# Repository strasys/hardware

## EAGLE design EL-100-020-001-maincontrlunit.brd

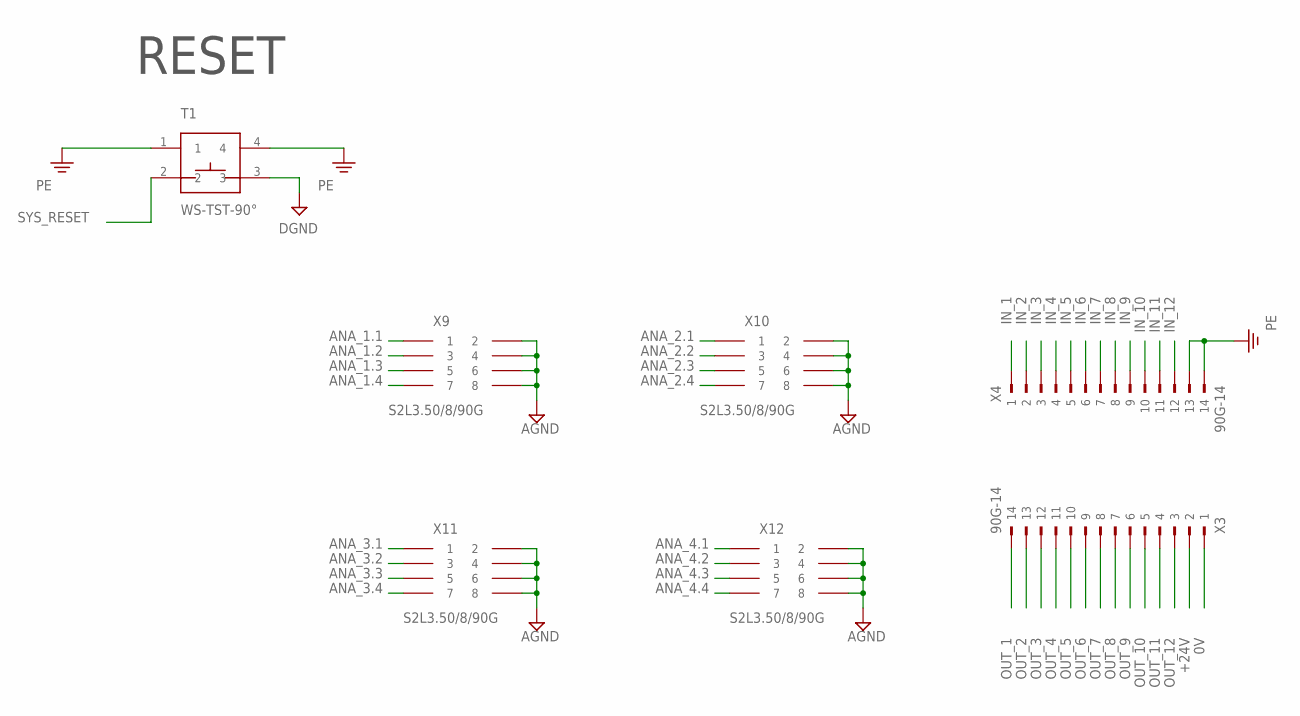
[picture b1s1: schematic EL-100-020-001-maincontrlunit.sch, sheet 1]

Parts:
T1: WS-TST-90°
X3, X4: 90G-14
X9, X10, X11, X12: S2L3.50/8/90G; S2L-90G-8

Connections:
0V: X3.1; also elsewhere on the board
+24V: X3.2; also elsewhere on the board
AGND: X9.2, X9.4, X9.6, X9.8, X10.2, X10.4, X10.6, X10.8, X11.2, X11.4, X11.6, X11.8, X12.2, X12.4, X12.6, X12.8; also elsewhere on the board
ANA_1.1: X9.1; also elsewhere on the board
ANA_1.2: X9.3; also elsewhere on the board
ANA_1.3: X9.5; also elsewhere on the board
ANA_1.4: X9.7; also elsewhere on the board
ANA_2.1: X10.1; also elsewhere on the board
ANA_2.2: X10.3; also elsewhere on the board
ANA_2.3: X10.5; also elsewhere on the board
ANA_2.4: X10.7; also elsewhere on the board
ANA_3.1: X11.1; also elsewhere on the board
ANA_3.2: X11.3; also elsewhere on the board
ANA_3.3: X11.5; also elsewhere on the board
ANA_3.4: X11.7; also elsewhere on the board
ANA_4.1: X12.1; also elsewhere on the board
ANA_4.2: X12.3; also elsewhere on the board
ANA_4.3: X12.5; also elsewhere on the board
ANA_4.4: X12.7; also elsewhere on the board
DGND: T1.3; also elsewhere on the board
IN_1: X4.1; also elsewhere on the board
IN_2: X4.2; also elsewhere on the board
IN_3: X4.3; also elsewhere on the board
IN_4: X4.4; also elsewhere on the board
IN_5: X4.5; also elsewhere on the board
IN_6: X4.6; also elsewhere on the board
IN_7: X4.7; also elsewhere on the board
IN_8: X4.8; also elsewhere on the board
IN_9: X4.9; also elsewhere on the board
IN_10: X4.10; also elsewhere on the board
IN_11: X4.11; also elsewhere on the board
IN_12: X4.12; also elsewhere on the board
OUT_1: X3.14; also elsewhere on the board
OUT_2: X3.13; also elsewhere on the board
OUT_3: X3.12; also elsewhere on the board
OUT_4: X3.11; also elsewhere on the board
OUT_5: X3.10; also elsewhere on the board
OUT_6: X3.9; also elsewhere on the board
OUT_7: X3.8; also elsewhere on the board
OUT_8: X3.7; also elsewhere on the board
OUT_9: X3.6; also elsewhere on the board
OUT_10: X3.5; also elsewhere on the board
OUT_11: X3.4; also elsewhere on the board
OUT_12: X3.3; also elsewhere on the board
PE: T1.1, T1.4, X4.13, X4.14; also elsewhere on the board
SYS_RESET: T1.2; also elsewhere on the board

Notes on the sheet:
RESET

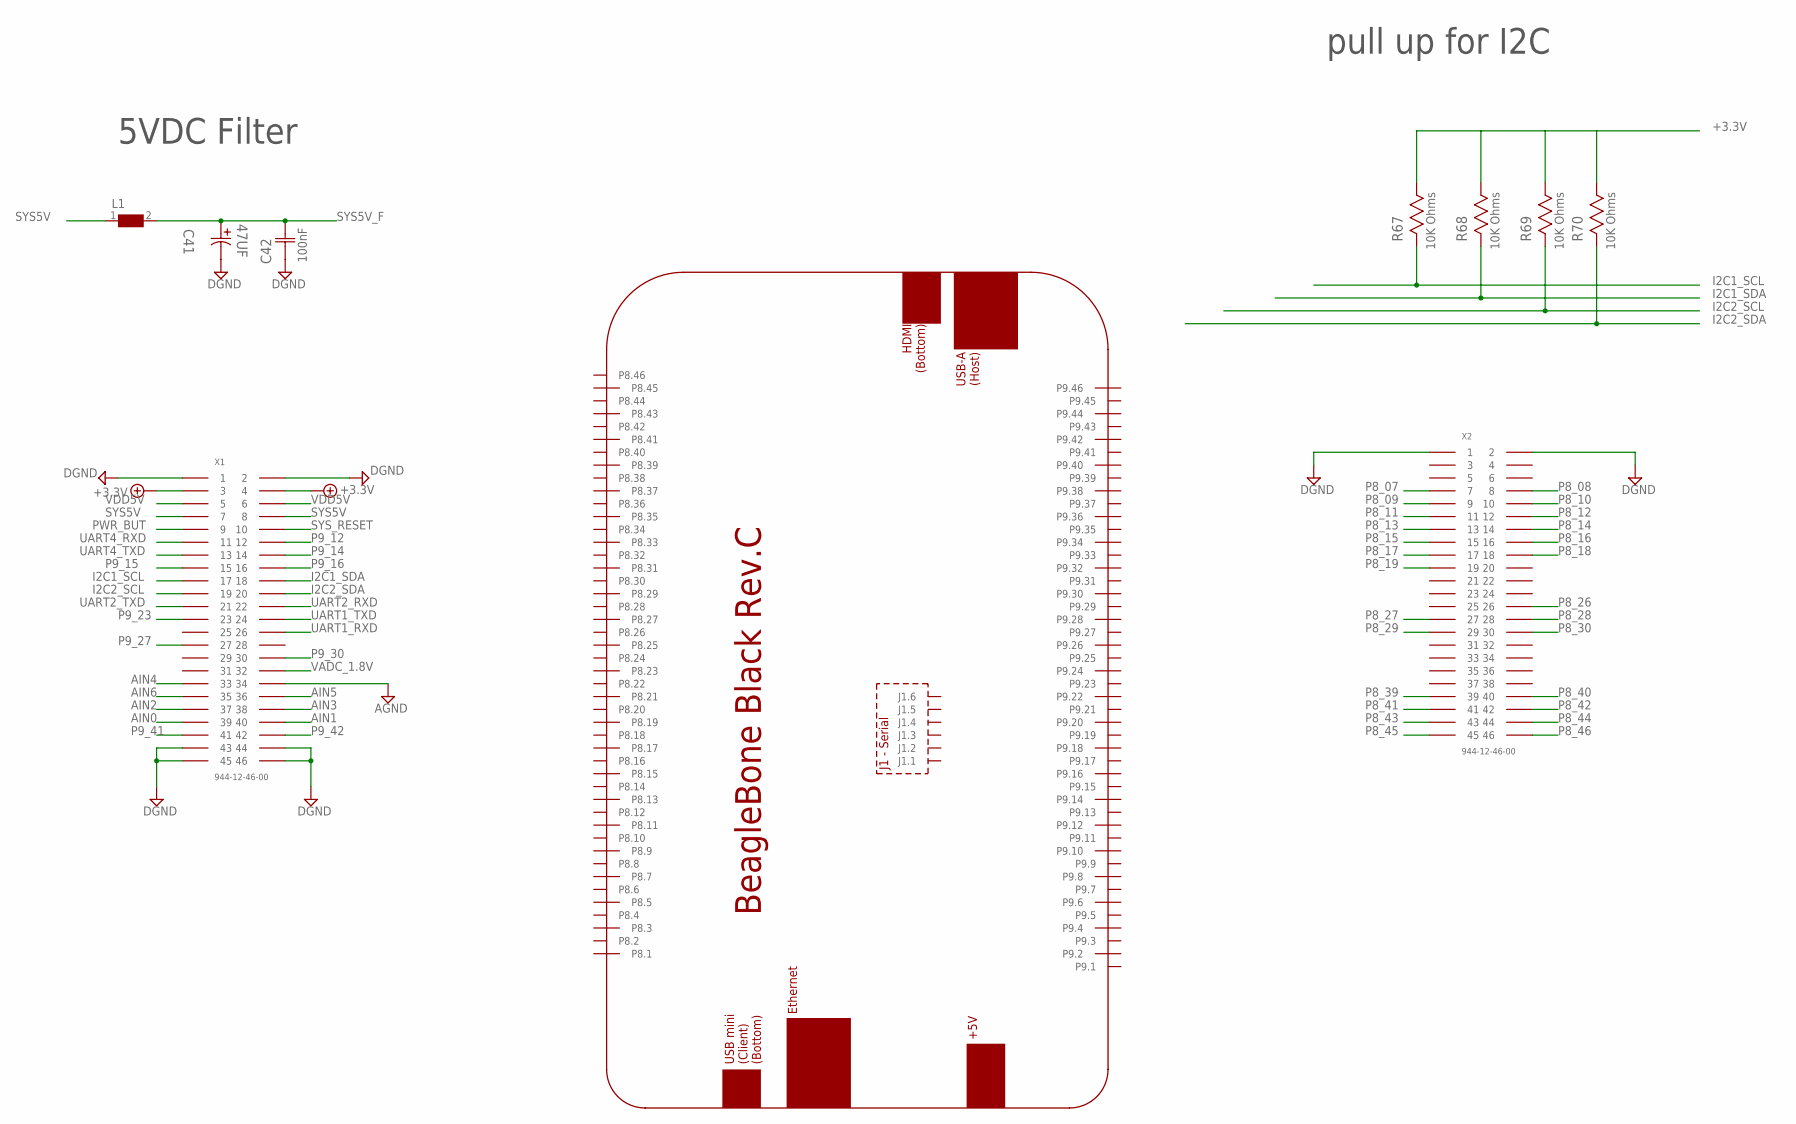
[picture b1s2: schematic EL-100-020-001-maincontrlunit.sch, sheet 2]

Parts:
C41: 47UF; CAPAE660X610N
C42: 100nF; CAPC2013X110N
L1: WE-CBF-74279218_1206; 1206
R67, R68, R69, R70: 10K Ohms; RESC2013X65N
X1, X2: 944-12-46-00; 2,54_STIFTLEIST_2X23

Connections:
+3.3V: R67.1, R68.1, R69.1, R70.1, X1.P3 (3), X1.P4 (4); also elsewhere on the board
AGND: X1.P34 (34); also elsewhere on the board
AIN0: X1.P39 (39); also elsewhere on the board
AIN1: X1.P40 (40); also elsewhere on the board
AIN2: X1.P37 (37); also elsewhere on the board
AIN3: X1.P38 (38); also elsewhere on the board
AIN4: X1.P33 (33); also elsewhere on the board
AIN5: X1.P36 (36); also elsewhere on the board
AIN6: X1.P35 (35); also elsewhere on the board
DGND: C41.2, C42.1 (C1), X1.P1 (1), X1.P2 (2), X1.P43 (43), X1.P44 (44), X1.P45 (45), X1.P46 (46), X2.P1 (1), X2.P2 (2); also elsewhere on the board
I2C1_SCL: R67.2, X1.P17 (17); also elsewhere on the board
I2C1_SDA: R68.2, X1.P18 (18); also elsewhere on the board
I2C2_SCL: R69.2, X1.P19 (19); also elsewhere on the board
I2C2_SDA: R70.2, X1.P20 (20); also elsewhere on the board
P8_07: X2.P7 (7); also elsewhere on the board
P8_08: X2.P8 (8); also elsewhere on the board
P8_09: X2.P9 (9); also elsewhere on the board
P8_10: X2.P10 (10); also elsewhere on the board
P8_11: X2.P11 (11); also elsewhere on the board
P8_12: X2.P12 (12); also elsewhere on the board
P8_13: X2.P13 (13); also elsewhere on the board
P8_14: X2.P14 (14); also elsewhere on the board
P8_15: X2.P15 (15); also elsewhere on the board
P8_16: X2.P16 (16); also elsewhere on the board
P8_17: X2.P17 (17); also elsewhere on the board
P8_18: X2.P18 (18); also elsewhere on the board
P8_19: X2.P19 (19)
P8_26: X2.P26 (26)
P8_27: X2.P27 (27); also elsewhere on the board
P8_28: X2.P28 (28); also elsewhere on the board
P8_29: X2.P29 (29); also elsewhere on the board
P8_30: X2.P30 (30); also elsewhere on the board
P8_39: X2.P39 (39); also elsewhere on the board
P8_40: X2.P40 (40); also elsewhere on the board
P8_41: X2.P41 (41); also elsewhere on the board
P8_42: X2.P42 (42); also elsewhere on the board
P8_43: X2.P43 (43); also elsewhere on the board
P8_44: X2.P44 (44); also elsewhere on the board
P8_45: X2.P45 (45); also elsewhere on the board
P8_46: X2.P46 (46); also elsewhere on the board
P9_12: X1.P12 (12)
P9_14: X1.P14 (14); also elsewhere on the board
P9_15: X1.P15 (15); also elsewhere on the board
P9_16: X1.P16 (16)
P9_23: X1.P23 (23)
P9_27: X1.P27 (27)
P9_30: X1.P30 (30)
P9_41: X1.P41 (41)
P9_42: X1.P42 (42)
PWR_BUT: X1.P9 (9)
SYS5V: L1.1, X1.P7 (7), X1.P8 (8)
SYS5V_F: C41.1, C42.2 (C2), L1.2; also elsewhere on the board
SYS_RESET: X1.P10 (10); also elsewhere on the board
UART1_RXD: X1.P26 (26)
UART1_TXD: X1.P24 (24)
UART2_RXD: X1.P22 (22)
UART2_TXD: X1.P21 (21)
UART4_RXD: X1.P11 (11)
UART4_TXD: X1.P13 (13)
VADC_1.8V: X1.P32 (32); also elsewhere on the board
VDD5V: X1.P5 (5), X1.P6 (6)

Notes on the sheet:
5VDC Filter
pull up for I2C

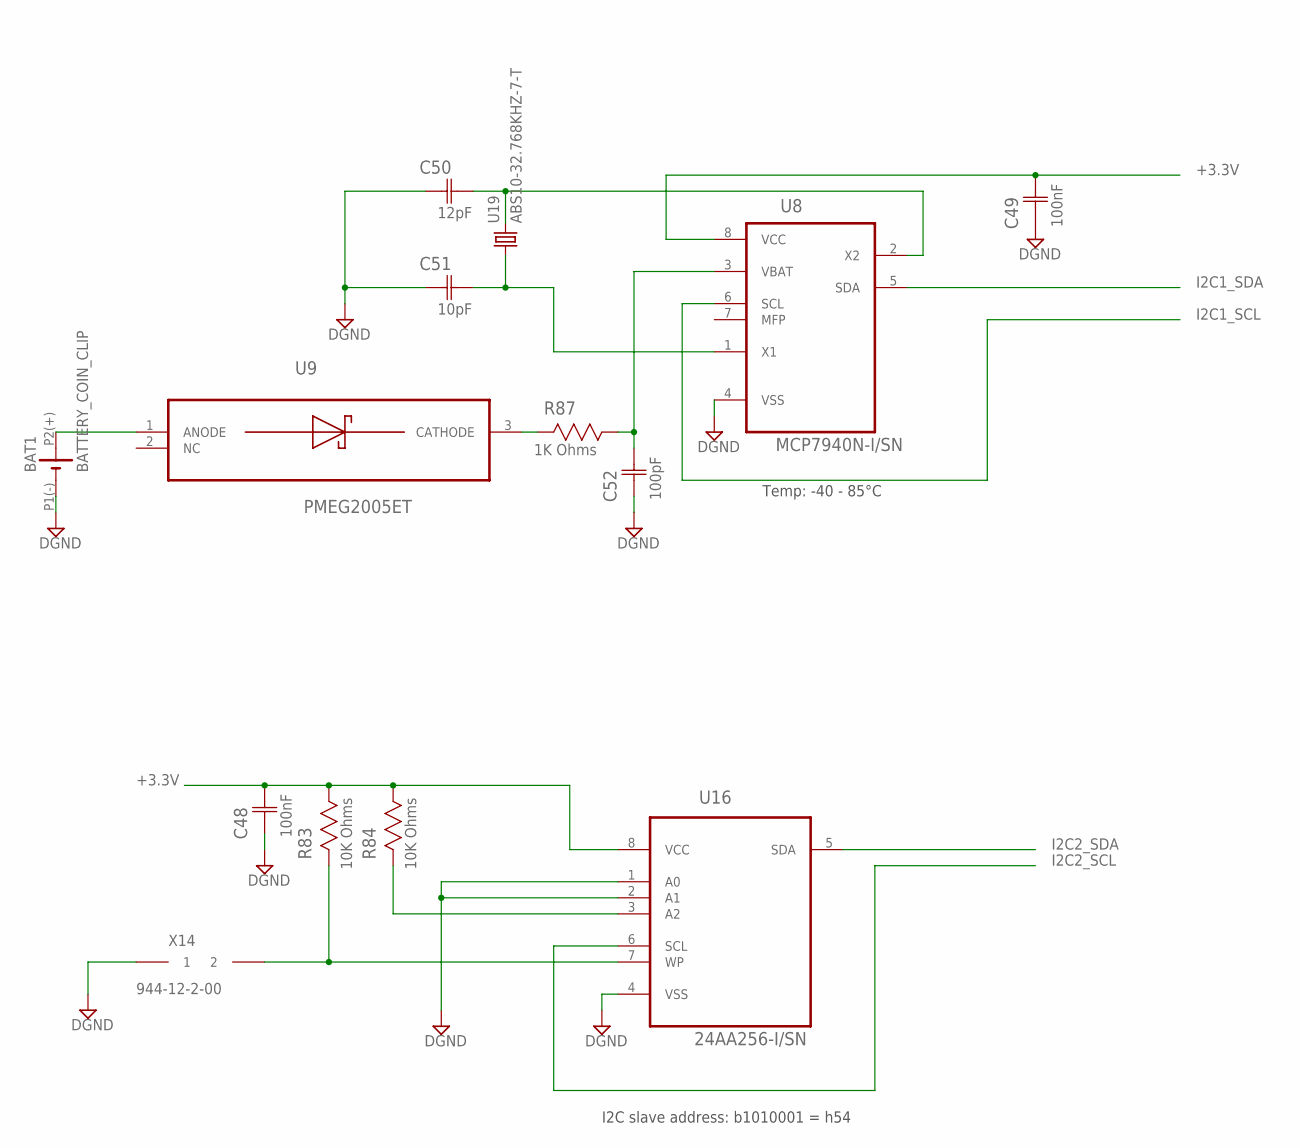
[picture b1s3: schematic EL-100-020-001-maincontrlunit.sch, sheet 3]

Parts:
BAT1: BATTERY_COIN_CLIP; BAT_HOLDER_16MM
C48, C49: 100nF; CAPC2013X110N
C50: 12pF; CAPC2013X88N
C51: 10pF; CAPC2013X88N
C52: 100pF; CAPC2013X88N
R83, R84: 10K Ohms; RESC2013X65N
R87: 1K Ohms; RESC2013X65N
U8: MCP7940N-I/SN; SOIC127P600X175-8N; MPN MCP7940N-I/SN
U9: PMEG2005ET; SOT95P280X145-5N
U16: 24AA256-I/SN; SOIC127P600X175-8N
U19: ABS10-32.768KHZ-7-T; ABS-10
X14: 944-12-2-00; 2,54_2X1

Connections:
24AA_WP: R83.2, U16.7 (WP), X14.P2 (2)
+3.3V: C48.2 (C2), C49.2 (C2), R83.1, R84.1, U8.8 (VCC), U16.8 (VCC); also elsewhere on the board
BAT-SUPPLY: BAT1.P2(+) (+), U9.1 (ANODE)
DGND: BAT1.P1(-) (-), C48.1 (C1), C49.1 (C1), C50.1 (C1), C51.1 (C1), C52.1 (C1), U8.4 (VSS), U16.1 (A0), U16.2 (A1), U16.4 (VSS), X14.P1 (1); also elsewhere on the board
I2C1_SCL: U8.6 (SCL); also elsewhere on the board
I2C1_SDA: U8.5 (SDA); also elsewhere on the board
I2C2_SCL: U16.6 (SCL); also elsewhere on the board
I2C2_SDA: U16.5 (SDA); also elsewhere on the board
unnamed: R84.2, U16.3 (A2)
unnamed: R87.2, U9.3 (CATHODE)
unnamed: C52.2 (C2), R87.1, U8.3 (VBAT)
unnamed: C50.2 (C2), U8.2 (X2), U19.P$2 (2)
unnamed: C51.2 (C2), U8.1 (X1), U19.P$1 (1)

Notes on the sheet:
Temp: -40 - 85°C
I2C slave address: b1010001 = h54

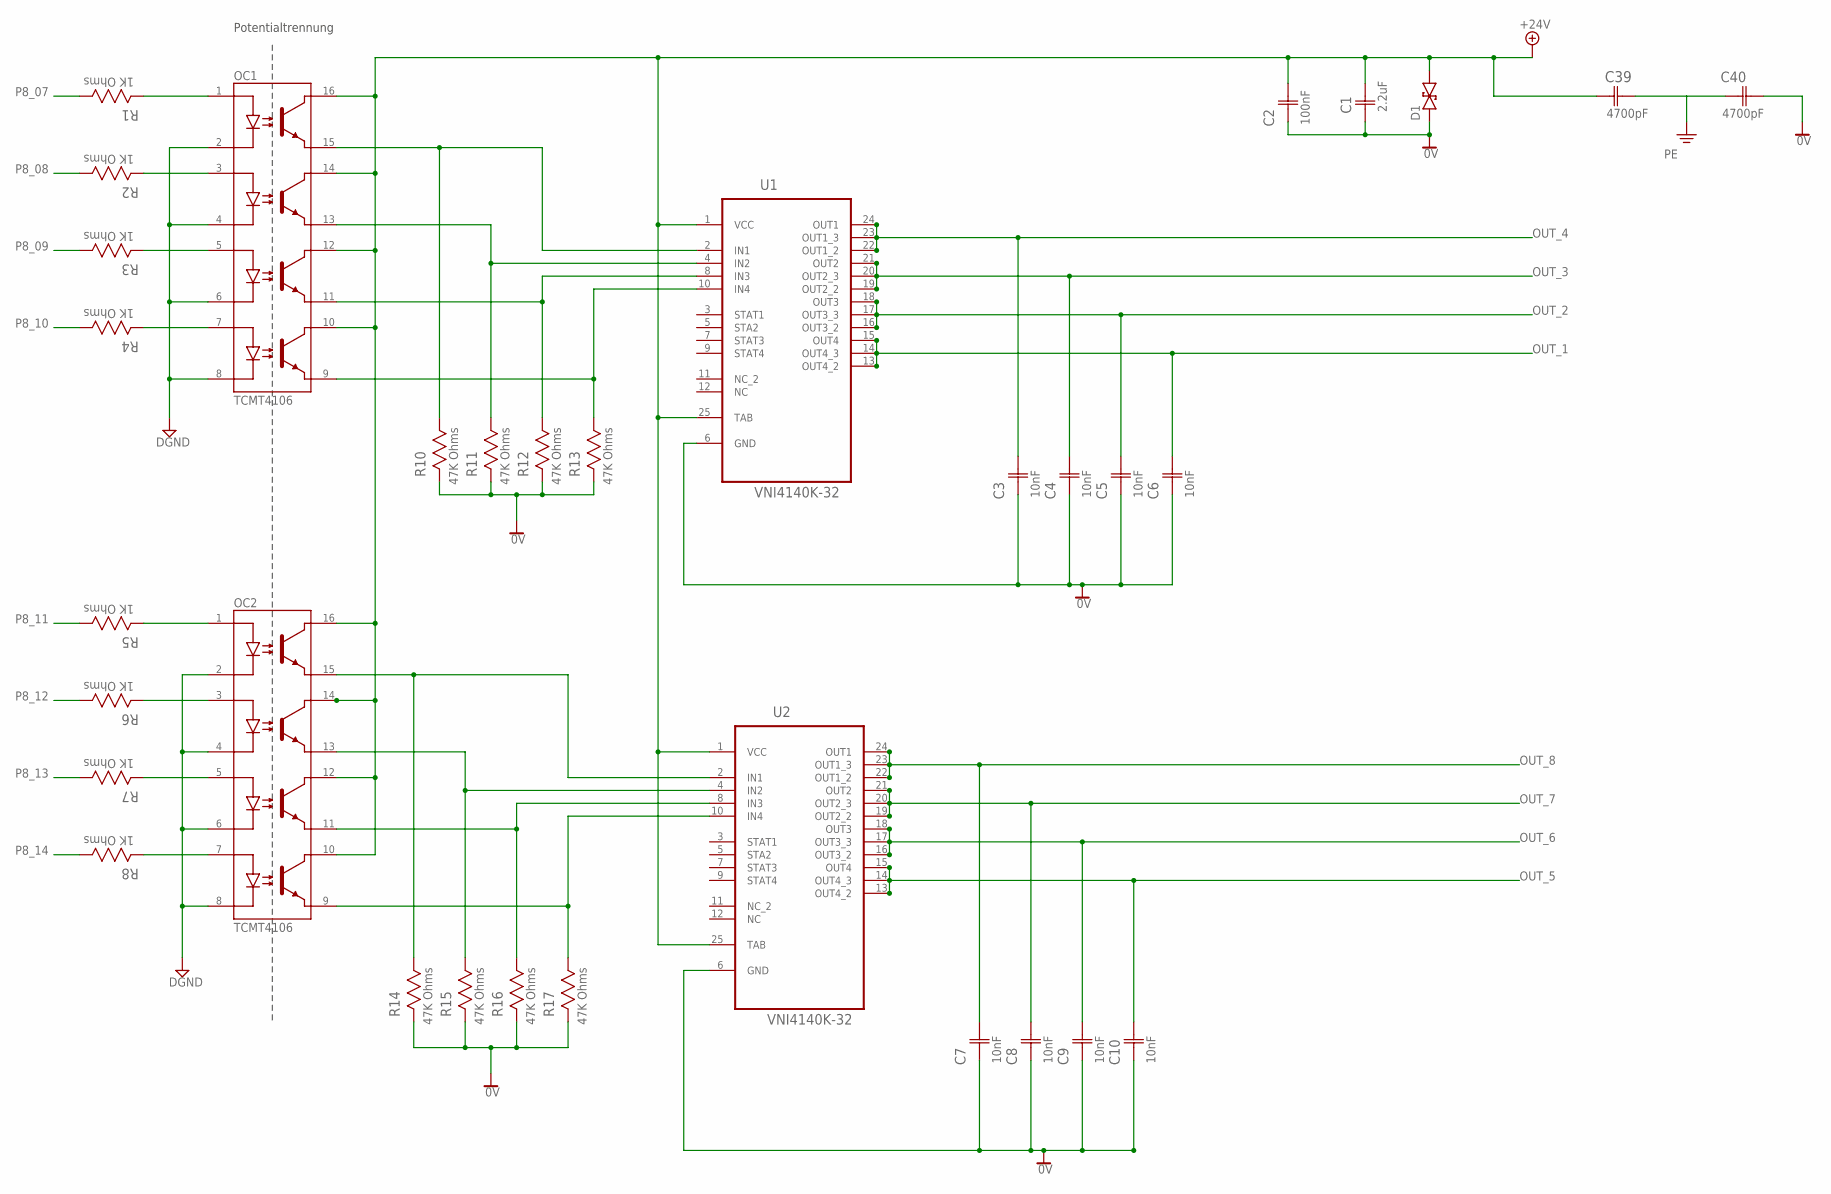
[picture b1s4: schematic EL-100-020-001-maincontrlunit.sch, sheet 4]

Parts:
C1: 2.2uF; CAPC3216X180N
C2: 100nF; CAPC2013X110N
C3, C4, C5, C6, C7, C8, C9, C10: 10nF; CAPC2013X88N
C39, C40: 4700pF; CAPC2013X88N
D1: SMA6J33CA; DO-214AC
OC1, OC2: TCMT4106; SOP-16
R1, R2, R3, R4, R5, R6, R7, R8: 1K Ohms; RESC2013X65N
R10, R11, R12, R13, R14, R15, R16, R17: 47K Ohms; RESC2013X65N
U1, U2: VNI4140K-32; SOP80P1030X247-25N

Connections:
0V: C1.1 (C1), C2.1 (C1), C3.1 (C1), C4.1 (C1), C5.1 (C1), C6.1 (C1), C7.1 (C1), C8.1 (C1), C9.1 (C1), C10.1 (C1), C40.2 (C2), D1.1, R10.2, R11.2, R12.2, R13.2, R14.2, R15.2, R16.2, R17.2, U1.6 (GND), U2.6 (GND); also elsewhere on the board
+24V: C1.2 (C2), C2.2 (C2), C39.1 (C1), D1.2, OC1.10, OC1.12, OC1.14, OC1.16, OC2.10, OC2.12, OC2.14, OC2.16, U1.1 (VCC), U1.25 (TAB), U2.1 (VCC), U2.25 (TAB); also elsewhere on the board
DGND: OC1.2, OC1.4, OC1.6, OC1.8, OC2.2, OC2.4, OC2.6, OC2.8; also elsewhere on the board
unnamed: OC1.5, R3.2
unnamed: OC1.7, R4.2
unnamed: OC2.3, R6.2
unnamed: OC2.5, R7.2
unnamed: OC2.7, R8.2
unnamed: OC1.1, R1.2
unnamed: OC1.3, R2.2
unnamed: OC1.15, R10.1, U1.2 (IN1)
unnamed: OC1.13, R11.1, U1.4 (IN2)
unnamed: OC1.11, R12.1, U1.8 (IN3)
unnamed: OC1.9, R13.1, U1.10 (IN4)
unnamed: OC2.1, R5.2
unnamed: OC2.15, R14.1, U2.2 (IN1)
unnamed: OC2.13, R15.1, U2.4 (IN2)
unnamed: OC2.11, R16.1, U2.8 (IN3)
unnamed: OC2.9, R17.1, U2.10 (IN4)
OUT_1: C6.2 (C2), U1.13 (OUT4_2), U1.14 (OUT4_3), U1.15 (OUT4); also elsewhere on the board
OUT_2: C5.2 (C2), U1.16 (OUT3_2), U1.17 (OUT3_3), U1.18 (OUT3); also elsewhere on the board
OUT_3: C4.2 (C2), U1.19 (OUT2_2), U1.20 (OUT2_3), U1.21 (OUT2); also elsewhere on the board
OUT_4: C3.2 (C2), U1.22 (OUT1_2), U1.23 (OUT1_3), U1.24 (OUT1); also elsewhere on the board
OUT_5: C10.2 (C2), U2.13 (OUT4_2), U2.14 (OUT4_3), U2.15 (OUT4); also elsewhere on the board
OUT_6: C9.2 (C2), U2.16 (OUT3_2), U2.17 (OUT3_3), U2.18 (OUT3); also elsewhere on the board
OUT_7: C8.2 (C2), U2.19 (OUT2_2), U2.20 (OUT2_3), U2.21 (OUT2); also elsewhere on the board
OUT_8: C7.2 (C2), U2.22 (OUT1_2), U2.23 (OUT1_3), U2.24 (OUT1); also elsewhere on the board
P8_07: R1.1; also elsewhere on the board
P8_08: R2.1; also elsewhere on the board
P8_09: R3.1; also elsewhere on the board
P8_10: R4.1; also elsewhere on the board
P8_11: R5.1; also elsewhere on the board
P8_12: R6.1; also elsewhere on the board
P8_13: R7.1; also elsewhere on the board
P8_14: R8.1; also elsewhere on the board
PE: C39.2 (C2), C40.1 (C1); also elsewhere on the board

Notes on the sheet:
Potentialtrennung

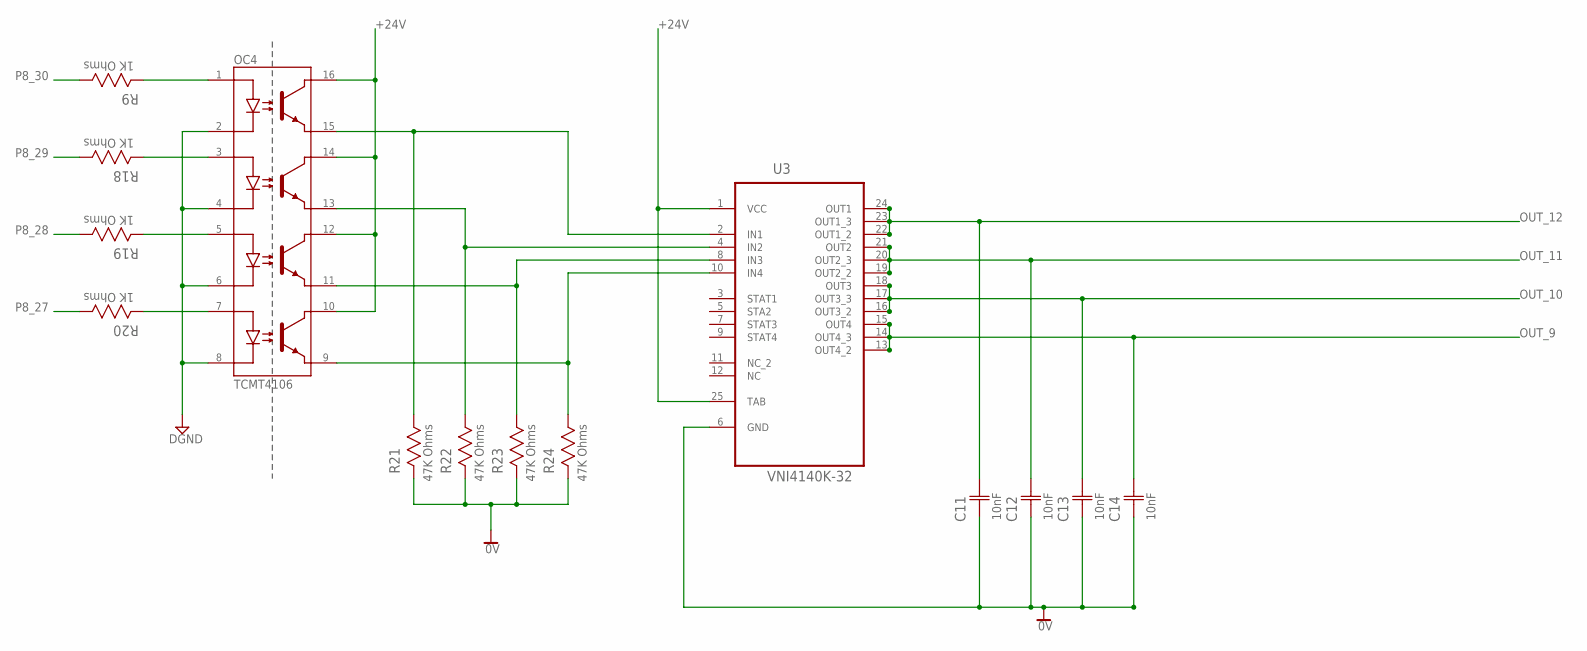
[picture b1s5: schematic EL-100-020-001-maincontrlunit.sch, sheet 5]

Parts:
C11, C12, C13, C14: 10nF; CAPC2013X88N
OC4: TCMT4106; SOP-16
R9, R18, R19, R20: 1K Ohms; RESC2013X65N
R21, R22, R23, R24: 47K Ohms; RESC2013X65N
U3: VNI4140K-32; SOP80P1030X247-25N

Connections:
0V: C11.1 (C1), C12.1 (C1), C13.1 (C1), C14.1 (C1), R21.2, R22.2, R23.2, R24.2, U3.6 (GND); also elsewhere on the board
+24V: OC4.10, OC4.12, OC4.14, OC4.16, U3.1 (VCC), U3.25 (TAB); also elsewhere on the board
DGND: OC4.2, OC4.4, OC4.6, OC4.8; also elsewhere on the board
unnamed: OC4.1, R9.2
unnamed: OC4.15, R21.1, U3.2 (IN1)
unnamed: OC4.13, R22.1, U3.4 (IN2)
unnamed: OC4.11, R23.1, U3.8 (IN3)
unnamed: OC4.9, R24.1, U3.10 (IN4)
unnamed: OC4.3, R18.2
unnamed: OC4.5, R19.2
unnamed: OC4.7, R20.2
OUT_9: C14.2 (C2), U3.13 (OUT4_2), U3.14 (OUT4_3), U3.15 (OUT4); also elsewhere on the board
OUT_10: C13.2 (C2), U3.16 (OUT3_2), U3.17 (OUT3_3), U3.18 (OUT3); also elsewhere on the board
OUT_11: C12.2 (C2), U3.19 (OUT2_2), U3.20 (OUT2_3), U3.21 (OUT2); also elsewhere on the board
OUT_12: C11.2 (C2), U3.22 (OUT1_2), U3.23 (OUT1_3), U3.24 (OUT1); also elsewhere on the board
P8_27: R20.1; also elsewhere on the board
P8_28: R19.1; also elsewhere on the board
P8_29: R18.1; also elsewhere on the board
P8_30: R9.1; also elsewhere on the board

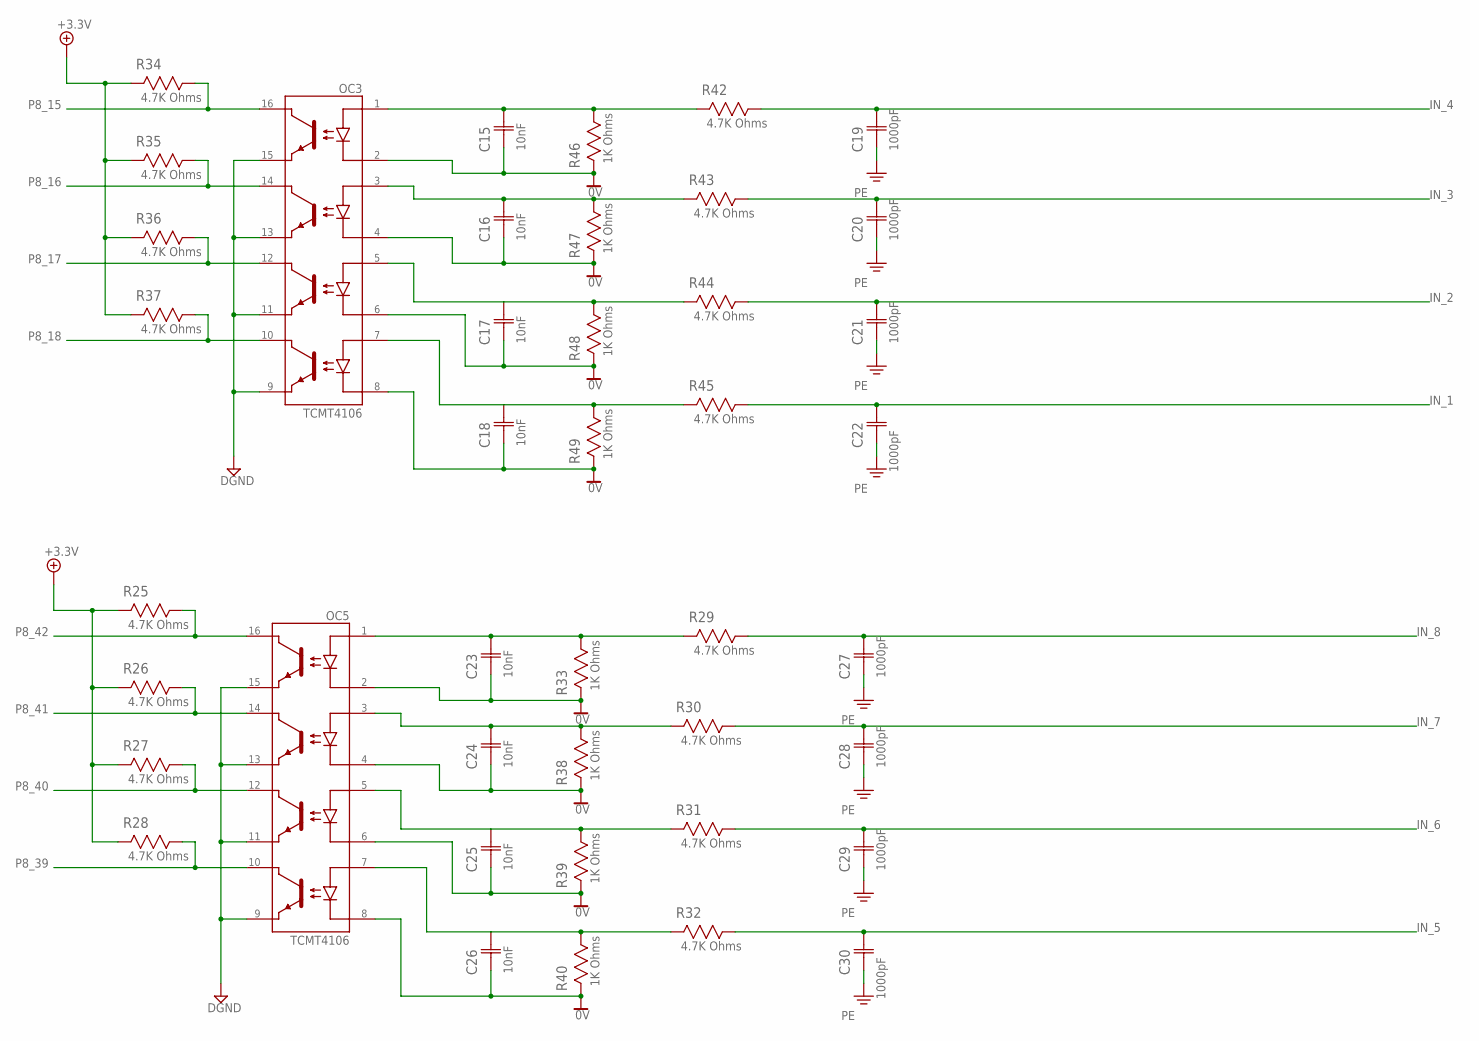
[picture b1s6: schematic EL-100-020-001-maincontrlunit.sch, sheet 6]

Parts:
C15, C16, C17, C18, C23, C24, C25, C26: 10nF; CAPC2013X88N
C19, C20, C21, C22, C27, C28, C29, C30: 1000pF; CAPC3216X88N
OC3, OC5: TCMT4106; SOP-16
R25, R26, R27, R28, R29, R30, R31, R32, R34, R35, R36, R37, R42, R43, R44, R45: 4.7K Ohms; RESC2013X65N
R33, R38, R39, R40, R46, R47, R48, R49: 1K Ohms; RESC2013X65N

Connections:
0V: C15.1 (C1), C16.1 (C1), C17.1 (C1), C18.1 (C1), C23.1 (C1), C24.1 (C1), C25.1 (C1), C26.1 (C1), OC3.2, OC3.4, OC3.6, OC3.8, OC5.2, OC5.4, OC5.6, OC5.8, R33.2, R38.2, R39.2, R40.2, R46.2, R47.2, R48.2, R49.2; also elsewhere on the board
+3.3V: R25.2, R26.2, R27.2, R28.2, R34.2, R35.2, R36.2, R37.2; also elsewhere on the board
DGND: OC3.9, OC3.11, OC3.13, OC3.15, OC5.9, OC5.11, OC5.13, OC5.15; also elsewhere on the board
IN_1: C22.2 (C2), R45.1; also elsewhere on the board
IN_2: C21.2 (C2), R44.1; also elsewhere on the board
IN_3: C20.2 (C2), R43.1; also elsewhere on the board
IN_4: C19.2 (C2), R42.1; also elsewhere on the board
IN_5: C30.2 (C2), R32.1; also elsewhere on the board
IN_6: C29.2 (C2), R31.1; also elsewhere on the board
IN_7: C28.2 (C2), R30.1; also elsewhere on the board
IN_8: C27.2 (C2), R29.1; also elsewhere on the board
unnamed: C23.2 (C2), OC5.1, R29.2, R33.1
unnamed: C24.2 (C2), OC5.3, R30.2, R38.1
unnamed: C25.2 (C2), OC5.5, R31.2, R39.1
unnamed: C26.2 (C2), OC5.7, R32.2, R40.1
unnamed: C15.2 (C2), OC3.1, R42.2, R46.1
unnamed: C16.2 (C2), OC3.3, R43.2, R47.1
unnamed: C17.2 (C2), OC3.5, R44.2, R48.1
unnamed: C18.2 (C2), OC3.7, R45.2, R49.1
P8_15: OC3.16, R34.1; also elsewhere on the board
P8_16: OC3.14, R35.1; also elsewhere on the board
P8_17: OC3.12, R36.1; also elsewhere on the board
P8_18: OC3.10, R37.1; also elsewhere on the board
P8_39: OC5.10, R28.1; also elsewhere on the board
P8_40: OC5.12, R27.1; also elsewhere on the board
P8_41: OC5.14, R26.1; also elsewhere on the board
P8_42: OC5.16, R25.1; also elsewhere on the board
PE: C19.1 (C1), C20.1 (C1), C21.1 (C1), C22.1 (C1), C27.1 (C1), C28.1 (C1), C29.1 (C1), C30.1 (C1); also elsewhere on the board

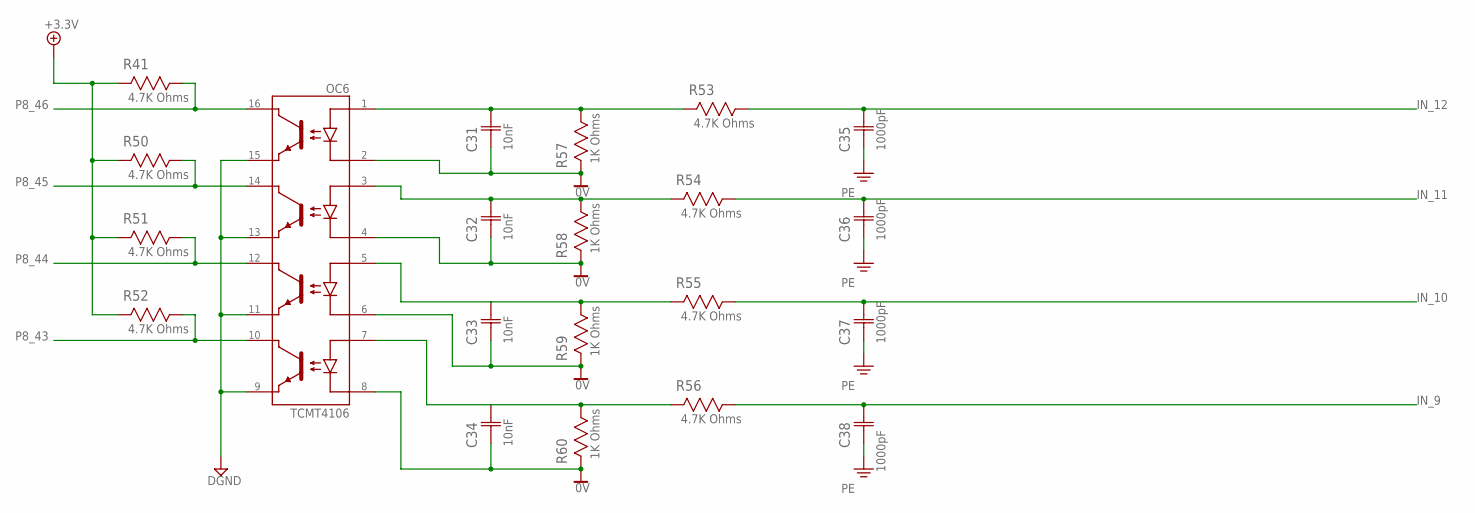
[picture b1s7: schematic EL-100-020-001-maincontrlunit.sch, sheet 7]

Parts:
C31, C32, C33, C34: 10nF; CAPC2013X88N
C35, C36, C37, C38: 1000pF; CAPC3216X88N
OC6: TCMT4106; SOP-16
R41, R50, R51, R52, R53, R54, R55, R56: 4.7K Ohms; RESC2013X65N
R57, R58, R59, R60: 1K Ohms; RESC2013X65N

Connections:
0V: C31.1 (C1), C32.1 (C1), C33.1 (C1), C34.1 (C1), OC6.2, OC6.4, OC6.6, OC6.8, R57.2, R58.2, R59.2, R60.2; also elsewhere on the board
+3.3V: R41.2, R50.2, R51.2, R52.2; also elsewhere on the board
DGND: OC6.9, OC6.11, OC6.13, OC6.15; also elsewhere on the board
IN_9: C38.2 (C2), R56.1; also elsewhere on the board
IN_10: C37.2 (C2), R55.1; also elsewhere on the board
IN_11: C36.2 (C2), R54.1; also elsewhere on the board
IN_12: C35.2 (C2), R53.1; also elsewhere on the board
unnamed: C31.2 (C2), OC6.1, R53.2, R57.1
unnamed: C32.2 (C2), OC6.3, R54.2, R58.1
unnamed: C33.2 (C2), OC6.5, R55.2, R59.1
unnamed: C34.2 (C2), OC6.7, R56.2, R60.1
P8_43: OC6.10, R52.1; also elsewhere on the board
P8_44: OC6.12, R51.1; also elsewhere on the board
P8_45: OC6.14, R50.1; also elsewhere on the board
P8_46: OC6.16, R41.1; also elsewhere on the board
PE: C35.1 (C1), C36.1 (C1), C37.1 (C1), C38.1 (C1); also elsewhere on the board

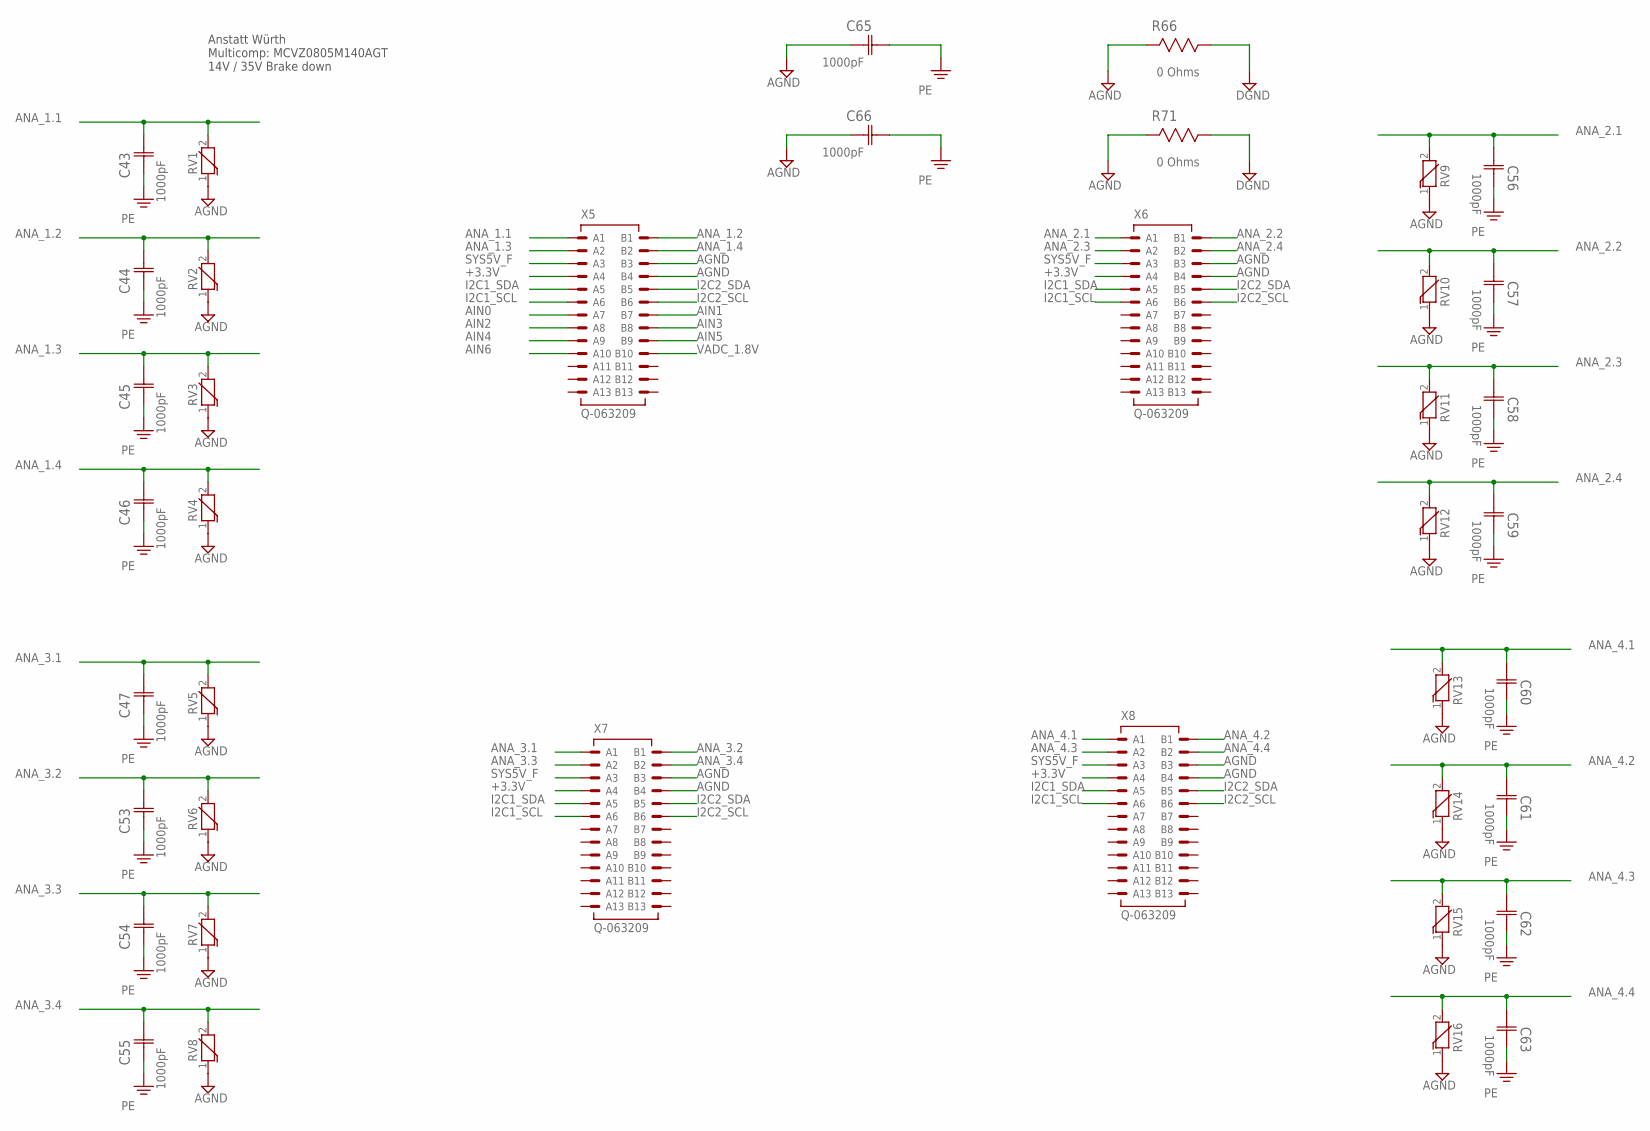
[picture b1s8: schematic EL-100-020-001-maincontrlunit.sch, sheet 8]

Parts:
C43, C44, C45, C46, C47, C53, C54, C55, C56, C57, C58, C59, C60, C61, C62, C63, C65, C66: 1000pF; CAPC3216X88N
R66, R71: 0 Ohms; RESC3216X71N
RV1, RV2, RV3, RV4, RV5, RV6, RV7, RV8, RV9, RV10, RV11, RV12, RV13, RV14, RV15, RV16: WE-VS-82550110_0805; WESURGE_0805
X5, X6, X7, X8: Q-063209; 063209

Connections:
+3.3V: X5.A4, X6.A4, X7.A4, X8.A4; also elsewhere on the board
AGND: C65.1 (C1), C66.1 (C1), R66.2, R71.2, RV1.1, RV2.1, RV3.1, RV4.1, RV5.1, RV6.1, RV7.1, RV8.1, RV9.1, RV10.1, RV11.1, RV12.1, RV13.1, RV14.1, RV15.1, RV16.1, X5.B3, X5.B4, X6.B3, X6.B4, X7.B3, X7.B4, X8.B3, X8.B4; also elsewhere on the board
AIN0: X5.A7; also elsewhere on the board
AIN1: X5.B7; also elsewhere on the board
AIN2: X5.A8; also elsewhere on the board
AIN3: X5.B8; also elsewhere on the board
AIN4: X5.A9; also elsewhere on the board
AIN5: X5.B9; also elsewhere on the board
AIN6: X5.A10; also elsewhere on the board
ANA_1.1: C43.2 (C2), RV1.2, X5.A1; also elsewhere on the board
ANA_1.2: C44.2 (C2), RV2.2, X5.B1; also elsewhere on the board
ANA_1.3: C45.2 (C2), RV3.2, X5.A2; also elsewhere on the board
ANA_1.4: C46.2 (C2), RV4.2, X5.B2; also elsewhere on the board
ANA_2.1: C56.2 (C2), RV9.2, X6.A1; also elsewhere on the board
ANA_2.2: C57.2 (C2), RV10.2, X6.B1; also elsewhere on the board
ANA_2.3: C58.2 (C2), RV11.2, X6.A2; also elsewhere on the board
ANA_2.4: C59.2 (C2), RV12.2, X6.B2; also elsewhere on the board
ANA_3.1: C47.2 (C2), RV5.2, X7.A1; also elsewhere on the board
ANA_3.2: C53.2 (C2), RV6.2, X7.B1; also elsewhere on the board
ANA_3.3: C54.2 (C2), RV7.2, X7.A2; also elsewhere on the board
ANA_3.4: C55.2 (C2), RV8.2, X7.B2; also elsewhere on the board
ANA_4.1: C60.2 (C2), RV13.2, X8.A1; also elsewhere on the board
ANA_4.2: C61.2 (C2), RV14.2, X8.B1; also elsewhere on the board
ANA_4.3: C62.2 (C2), RV15.2, X8.A2; also elsewhere on the board
ANA_4.4: C63.2 (C2), RV16.2, X8.B2; also elsewhere on the board
DGND: R66.1, R71.1; also elsewhere on the board
I2C1_SCL: X5.A6, X6.A6, X7.A6, X8.A6; also elsewhere on the board
I2C1_SDA: X5.A5, X6.A5, X7.A5, X8.A5; also elsewhere on the board
I2C2_SCL: X5.B6, X6.B6, X7.B6, X8.B6; also elsewhere on the board
I2C2_SDA: X5.B5, X6.B5, X7.B5, X8.B5; also elsewhere on the board
PE: C43.1 (C1), C44.1 (C1), C45.1 (C1), C46.1 (C1), C47.1 (C1), C53.1 (C1), C54.1 (C1), C55.1 (C1), C56.1 (C1), C57.1 (C1), C58.1 (C1), C59.1 (C1), C60.1 (C1), C61.1 (C1), C62.1 (C1), C63.1 (C1), C65.2 (C2), C66.2 (C2); also elsewhere on the board
SYS5V_F: X5.A3, X6.A3, X7.A3, X8.A3; also elsewhere on the board
VADC_1.8V: X5.B10; also elsewhere on the board

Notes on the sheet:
Anstatt Würth Multicomp: MCVZ0805M140AGT 14V / 35V Brake down

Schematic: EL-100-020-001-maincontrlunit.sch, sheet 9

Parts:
C64: 10nF; CAPC2013X88N
OC7: TCMT4106; SOP-16
R61: 4.7K Ohms; RESC2013X65N
R62, R63, R64, R65: 1K Ohms; RESC2013X65N
X13: 140-08-FLACHBAND1.27; 2,54_2X8

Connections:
0V: C64.1 (C1), OC7.2, R62.2; also elsewhere on the board
+24V: R61.1; also elsewhere on the board
+24V_ON: OC7.15, X13.P2 (2)
DGND: OC7.4, OC7.6, OC7.8, X13.P1 (1); also elsewhere on the board
ERROR: OC7.9, X13.P5 (5)
HEARTBEAT: OC7.11, X13.P4 (4)
unnamed: C64.2 (C2), OC7.1, R61.2, R62.1
unnamed: OC7.5, R63.2
unnamed: OC7.7, R64.2
P9_14: R63.1; also elsewhere on the board
P9_15: R64.1; also elsewhere on the board
SYS5V_F: OC7.3, OC7.10, OC7.12, OC7.14, OC7.16, R65.1, R65.2; also elsewhere on the board
SYS5V_ON: OC7.13, X13.P3 (3)
